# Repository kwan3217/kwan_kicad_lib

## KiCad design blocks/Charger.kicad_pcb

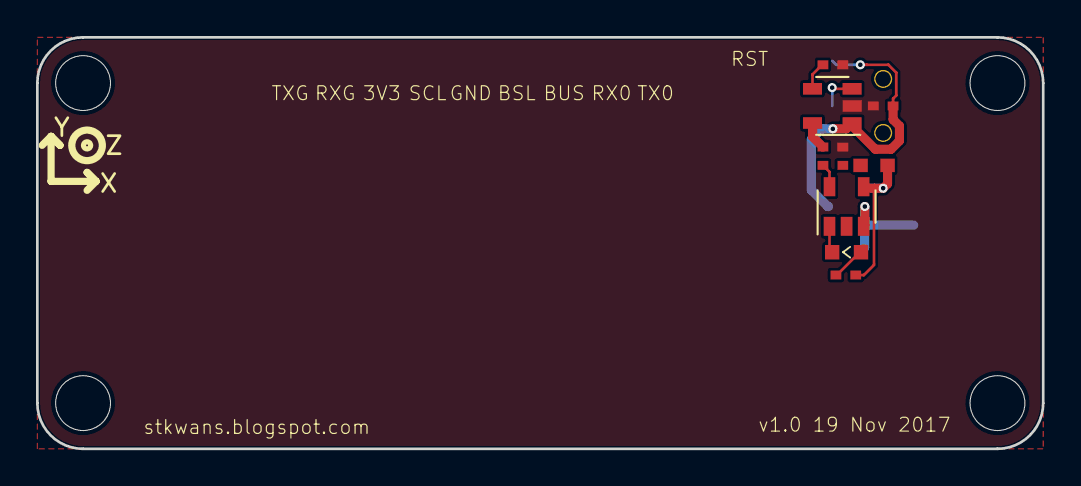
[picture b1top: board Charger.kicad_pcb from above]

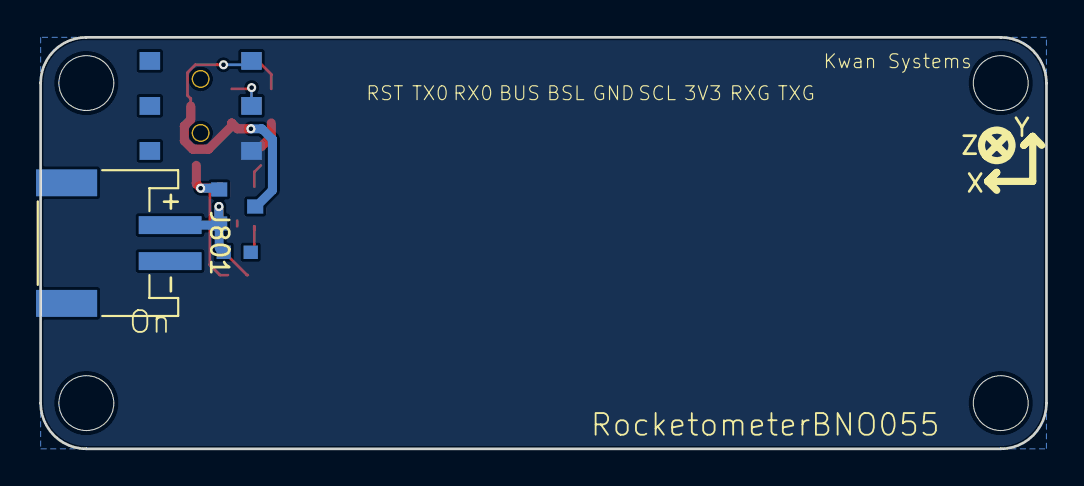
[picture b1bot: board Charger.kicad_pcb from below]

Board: 2 copper layers, 55.9 x 22.9 mm, 18 parts (4 on the bottom side), 11 nets.

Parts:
C704: 1uF; SMD_0402
C714: 100nF; SMD_0402
C715: 4.7nF; SMD_0402
C802, C803: 4.7uF; SMD_0603
D801: YELLOW; D_0603
D802: DCC; SOT-23
J801: JST 2mm; SPARKFUN_JST_POWER
JP1, JP2, JP4, JP5: STAND-OFFTIGHT; STAND-OFF-TIGHT
R801: 10k; SMD_0402
R804: 1.5k; SMD_0402
S701: SPDT; SWITCH_DPDT_AZY0202
U501: MPU9250; Axis
U701: 3.3V; SOT-23-5
U801: MCP73831; SOT-23-5

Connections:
/GND: C802.2, C803.2, J801.-, R801.1, U801.2
/PROG: R801.2, U801.5
/Regulator/BYP: C714.1, U701.4
/Regulator/PWR_EN: S701.2, U701.3
/STAT+: D801.2, R804.2
/STAT-: D801.1, U801.1
/VBUS: C802.1, D802.1, R804.1, U801.4
/VLIPO: C803.1, D802.2, J801.+, U801.3
/VRAW: C704.1, D802.3, S701.1, U701.1
GND: C704.2, C714.2, C715.2, S701.3, U701.2
VCC: C715.1, U701.5

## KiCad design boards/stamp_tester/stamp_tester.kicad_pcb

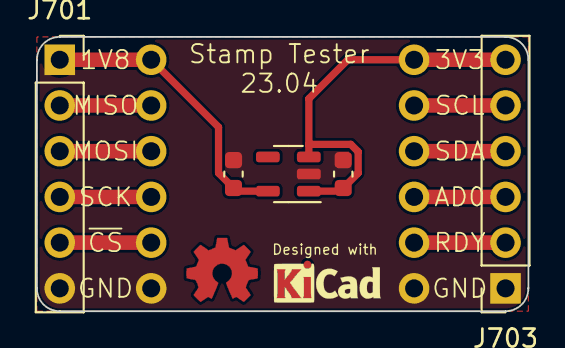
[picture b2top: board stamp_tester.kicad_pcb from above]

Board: 2 copper layers, 27.3 x 15.2 mm, 10 parts (1 on the bottom side), 11 nets.

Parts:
C801, C805: 1uF; C_0603_1608Metric
G701: github.com/kwan3217; KWAN_CIRCLE
G702: Designed with; Symbol_KiCAD-Logo_CopperAndSilkScreenTop_small
G703: OSHW; OSHW-Symbol_4x3.6mm_SolderMask
J701, J703: Conn_01x06_Pin; PinSocket_1x06_P2.54mm_Vertical
J702, J704: Conn_01x06_Pin; PinHeader_1x06_P2.54mm_Vertical
U801: TCR2EF 1.8V; SOT-23-5

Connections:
/Q_1V8: C805.1, J701.1, J702.1, U801.5 (OUT)
/Q_3V3: C801.1, J703.6, J704.6, U801.1 (IN), U801.3 (EN)
/Q_AD0: J703.3, J704.3
/Q_DRDY: J703.2, J704.2
/Q_GND: C801.2, C805.2, J701.6, J702.6, J703.1, J704.1, U801.2 (GND)
/Q_MISO: J701.2, J702.2
/Q_MOSI: J701.3, J702.3
/Q_SCK: J701.4, J702.4
/Q_SCL: J703.5, J704.5
/Q_SDA: J703.4, J704.4
/Q_~CS: J701.5, J702.5

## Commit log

2021-09-28 Refactored Kwan Systems library, ready to split to new repository
2021-09-28 Filtered repository and rerooted folder tree
2021-09-28 Pulling in things that hadn't been checked in before in old repo
2021-09-28 Corrected permissions
2021-09-28 Added a README.md to list files with cryptic names
2021-09-28 Added .gitignore
2021-09-28 Moved Teensy models
2021-09-28 Added notes for GCT connectors
2021-09-28 Added more parts to README.md
2021-09-29 Added RP2040_minimal. Added Arduino32U4. Made a controllers/ folder
2021-09-29 Added PicoDisplayPack
2022-04-18 Added backups and .dcm (legacy schematic documentation, empty in our case) files to be ignored
2022-04-18 Changed axis symbol to have Z axis circle at intersection of x and y axis. This allows the symbol to be smaller.
2022-04-18 Added reference to model from standard KiCad 3D lirary
2022-04-18 Added copper layer so that exposed copper is electrically isolated from ground plane
2022-04-18 Changed library to KiCad 6 format
2022-04-18 Changed references from one specific to a sheet, to unknown
2022-04-18 Add USB MidMount, to be used in Wearable Pocketometer 22.06
2022-04-18 Update StKwansSoldermask.kicad_mod
    Isolate exposed copper from ground plane
2022-04-18 Isolate exposed copper from ground plane
2022-04-18 Create SMA-EDGE.kicad_mod
    Stolen from Sparkfun ZED-F9P breakout, translated from Eagle to KiCad 6.0
2022-04-18 Added footprints for sensors to be used on Wearable Pocketometer 22.06
2022-04-18 Footprint for ICM-42688
2022-04-18 Connector compatible with quiic
2022-04-18 Updated footprints to include proper references to 3D models
2022-04-18 Update .gitignore
    Changed wildcard to catch more backup files
2022-04-18 Added reference for new Amphenol USB connector
2022-04-19 Added BMP384 model, and re-added a couple of stp models
2022-04-19 Added a readme describing how to export OpenSCAD to something KiCad can use
2022-04-19 Imported footprint from Package_CSP:WLCSP-12_1.56x1.56mm_P0.4mm so that I could assign my model to it
2022-04-19 Updated text objects
2022-04-19 Updated references to 3D models
2022-04-19 Updated models to use relative paths to 3D models
2022-04-19 Removed empty symbol
2022-04-19 Added graphics to Axis, KwanSystems, and OSHW symbols
2022-04-19 Added graphic for Kicad
2022-04-19 Added legacy BOM maker for Digikey
2022-04-20 Changed purely-graphical symbols to not appear in BOM
2022-04-20 Moved invisible NC pins off the grid
    This makes it so that when they get a NC symbol, they are not connected to each other
2022-04-20 Changed widths of graphics elements from 0 to thin
    Zero means follow the default, which is decidedly not zero.
2022-04-20 Changed terminal to polygonal
    Now a polygon, instead of a rectangle surrounded by a polygon that always tripped the DRC.
2022-04-20 Added symlinks to Kicad Python libraries for BOM script
2022-04-20 Bug fix -- include a missed variable initialization
2022-04-20 Changed so that all elements are grouped on Digikey number
    This is all Digikey cares about, so it is the right thing to group on in this context.
2022-04-20 Add pyc files to .gitignore
2022-04-20 Added corner silkscreen
    Corner silkscreens help confirm alignment, and may actually help the part center itself.
2022-04-25 Added JS5208 joystick
2022-04-25 Added USB cable footprint
    This is designed to be used as a BOM-only part, so we have a Digikey number for it but no reference on the board.
2022-04-25 Updated edge cut
    Changed an edge of the edge cut to a drill slot, to get those two little semicircular cutouts.
2022-04-25 Added footprint and model for joystick
2022-04-25 Added script to generate a BOM grouped on Digikey number
    This script is grouped on Digikey number, but includes columns for other fields
2022-04-28 Renamed pins from number to name
2022-04-28 Moved silkscreen corner marks so they just barely bracket the device
2022-04-28 Updated device
    Moved silkscreen corner marks so they just barely bracket the device. This device doesn't have the pin pattern centered on the package center, so package markings moved.
2022-04-28 Added footprint for JS1400 switch
2022-04-28 Added 3D model for TeensyView display
2022-04-28 Changed cutout to use a drill slot
2022-04-28 Added model for JS1400
2022-04-28 Added better model for Teensy 4.1
    The problem is, it takes 9 seconds to load.
2022-10-08 Added Raspberry Pi 4 model
2022-12-13 Updated several components
2022-12-13 Imported 1.8v regulator from rollercoasterometer
2022-12-13 Updated ADXL375 sensor schematic to Kicad 6.0
2022-12-13 Updated references
2022-12-13 Received ICM-20948 from rocketometer teensy
2022-12-13 Updated to Kicad 6
2022-12-14 Imported ICM-42688 from rollercoasterometer
2022-12-18 Added a standoff that matches the holes in the Raspberry Pi 4 -- no solder mask, no copper
2023-03-10 Added LED bar-graph
2023-03-10 Added LED bar graph
2023-03-10 Updated number on hand
2023-03-14 Updated to KiCad 7.0
2023-03-14 Added BME60.step and qwiic.step
2023-03-19 Added Sparkfun breakouts
2023-03-19 Pull in footprints for Sparkfun breakout boards
2023-03-19 Added breakout for ZED-F9R
2023-03-21 Updated to Kicad 7
2023-03-21 Added stamp footprints
2023-03-21 Updated to Kicad 7, added 3D model
2023-03-21 Added model and SMD pads for pin sockets
2023-03-21 Changed capacitors to 0603
2023-04-03 Changed to 0603 capacitors
2023-04-09 Updated number on hand, and added more Digikey/Mouser/Mfg numbers
2023-04-19 Separated out from Shipometer. No changes other than changing reference numbers.
2023-04-19 Change names of some pins in RPi_40 (add UART3 references)
2023-04-19 Renamed PiHAT to PiHat_NoSlot_Wide, to allow namespace for the other 3 variations of the PiHat board
2023-04-19 Added the other 3 variations of PiHAT board
2023-04-19 Changed pads to not have solder paste, since these will be hand-soldered. Moved pin labels to silkscreen.
2023-06-18 Updated with references to stamp tester
2023-06-18 Added two controllers
2023-06-18 Added USB stuff
2023-06-18 Added another controller
2023-06-18 Added ADXL375 sensor
2023-07-16 Use the separate hand sheets
2023-07-16 Added side dome LEDs
2023-07-16 Made a copy of regulator that is 3.3V
2023-07-17 Added LED footprint with pins labeled A and C, to match legacy Precision
2023-07-17 Added RESET pin, updated references to LED part numbers
2023-07-17 Added LED symbol with pins labeled A and C, for compatibility with legacy Precision
2023-10-16 Updating gitignore
2023-11-06 Added new footprints
2023-11-06 Added ICSP block to Arduino Nano. Added stamp
2023-11-06 Added Samtec pin header 01x06 SMT right angle. Added USB_C GCT USB4150. Added MiniStamp stuff.
2023-11-06 Updated ArduinoNano to Kicad7
2023-11-06 Corrected capacitor which should have been connected but wasn't
2023-11-06 Added source for model for 6-pin SMT right angle header
2023-11-12 Updated LED-0603-AC.kicad_mod
2023-11-12 Changed pin labeling to single-digit
2023-11-12 Changed analog and digital I/O to buses
2023-11-12 Added SAMTEC TSM-102. Updated README.
2023-11-14 Added labels for alternate purposes of pins
2023-11-14 Updated reference to 3D model
2023-11-21 Change to 8MHz crystal
2023-11-21 Add courtyard
2023-11-21 Added (unfinished) blocks for LPC2378 and ATMEGA32U4. Verify before using!
2023-11-23 Add text references Cx20 etc to support re-numbering the components when imporing into a different project.
2023-11-25 Add NMOS_DUAL_COMMON_SOURCE. We won't end up using it.
2023-11-25 Add PMOS_DUAL. We won't end up using it.
2023-11-25 Add Nano castellated slot and SMT pin header socket.
2023-12-06 Continue wiring MOSFET switches
2025-12-29 Convert to Kicad 9
2025-12-29 Updated to Kicad 9
2025-12-29 Added new blocks and sensors
2025-12-29 Added more sensors
2025-12-29 Updated .gitignore
